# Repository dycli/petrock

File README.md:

# Petrock

A split choc keyboard with a trackpoint in place of an outer thumb key:
**Petrock-41** has one, at the right thumb; **Petrock-40** has one on each half;
**Petrock-42** has none, a key at both outer thumbs.

Based on holykeebs' Corne Choc PCB and plate from
[idank/keyboards](https://github.com/idank/keyboards) (`corne/choc`, commit
f149b9b), licensed CC-BY-SA-4.0. This derivative uses the same licence.

## Changes from the Corne Choc

The board is built from the stock file: its parts move to the new layout, and
every wire is then drawn afresh by rule (see Build). The stock schematic's
connections stay, apart from the thumbs' columns (see Firmware).

- **No lighting.** Every per-key and underglow LED, the LED supply diodes and
  the LED wiring are gone (`tools/no_leds.py`). An RGB version may follow.
- **Exact stagger.** Rows exactly 17 mm apart, each column's top key a whole
  number of 2.37 mm steps below the middle finger's (`tools/stagger.py`;
  stock is off by up to 0.02 mm).
- **Five columns.** The outer pinky column goes. The pinky column moves up to
  one step below the ring column and gains a fourth key (the old outer top
  key); the ring column gains one too (the old outer bottom key). Each joins
  the column wire it lands on, in the thumb row (row 3).
- **Thumb cluster.** Each thumb key turns 15 degrees from its neighbour about a
  hinge where their facing corners sit 0.5 mm apart, starting from the bottom
  inner-index key (`tools/thumbs.py`). The 1.5u inner key becomes two 1u keys;
  the new upper one takes the thumb row's last free column (col 0).
- **Trackpoint.** Sprintek SK8707-01-004 at the outer thumb key: sensor on the
  front, nub centred on where the key was, driver on the back, PS/2 clock and
  data on controller pins 1/2, 3.3 V from the OLED header; sensor A1/A3, controller
  board A2/A4 (`tools/outer_thumb.py`, footprints from `tools/make_footprints.py`).
- **Pins for wireless.** Pins 1/2 are a nice!nano's high-frequency D1/D0, which
  the ZMK PS/2 driver recommends (lower-frequency pins can disturb Bluetooth);
  the TRRS data line moves from pin 2 to pin 11 to free them (`tools/pins.py`).
- **Outline.** Drawn from the keys (`tools/outline.py`): a flat top 1.15 mm
  above the middle column, 7.5-degree slopes to either side, a straight outer
  side, one 7.5-degree bottom edge, and the inner side widened for the upper
  thumb key (`tools/widen.py`). Keycaps sit 1.15 mm from the edge wherever it
  follows them.
- **Controller corner.** Across the strip between the inner index keycaps
  and the inner edge, the controller (a nice!nano's 17.78 mm board) and the
  jack's 6 mm body sit with three even 1.63 mm gaps; each drops until its square
  top corner is 1.15 mm inside the inner slope, like the keycaps. The USB-C and
  the jack's barrel overhang. The reset button sits under the jack
  (`tools/inner_strip.py`).
- The holykeebs and Corne logos and holykeebs' revision stamp are removed; the back
  carries the short hash of the commit the board was built from, between each
  controller's pin rows (`tools/stamp.py`; the build won't stamp uncommitted
  scripts); the board and the switch plates
  carry the Petrock logo with a 7 mm dot in its notch (`tools/logo.py`), and the
  jack, reset button and OLED header have no printed outlines
  (`tools/quiet_silk.py`).
- Five standoffs per half, as stock, placed by geometry (`tools/standoffs.py`):
  four where four keys meet, each at the four keys' centre, forming a 54 x 34 mm
  rectangle (pinky and ring columns, and index and inner index columns, each
  between their top two rows and below their third); and one at the thumbs,
  equally far from its three keycap corners. A key diode may move a fraction to
  make room, if it stays clear. The switch plate has a screw hole over each
  (`tools/plate.py`), as stock.
- Plates regenerated (`tools/plate.py`): the right one (both, on Petrock-40;
  neither, on Petrock-42) has an opening for the trackpoint sensor; a new FR4 bottom plate fits the
  outline.

## Build

`tools/build.sh [single|dual|none]` regenerates a board from the stock file:

1. **Place:** strip the lighting, then move every part to the layout
   (`tools/parts.py drag`).
2. **Route by rule** (`tools/route.py`), as a careful hand would: each column a
   straight line up the front through its switch pins; each row a line along
   the back under its keys, stepping 45 degrees in the gap between columns;
   every diode in the same place beside its key with the same two short links;
   the column wires gathered into an evenly spaced bus in the gap under the
   middle row and fanned into the controller in a staircase; the trackpoint
   wires and power in a bundle up the lane between the middle and index
   columns and along the top edge; every bend 45 degrees, no right angles
   except where a wire joins another. Then ground is poured on both sides and
   stitched together with vias (`tools/stitch.py`).
3. **Check:** the build fails unless DRC finds nothing but the stock
   footprints' library notices and every connection is made.

Then `tools/plates.sh` makes the plates (order the switch plates at 1.2 mm,
which choc switches clip into; the main board and bottom plate at 1.6 mm; all
in HASL, the cheapest finish: the trackpoint driver's pads are hand-soldered
and wide enough that ENIG's flatness isn't needed)
and the 1:1 printout (print it with
scaling off, e.g. `lp -o print-scaling=none`). `tools/fab.sh [single|dual|none]`
writes Gerber and drill zips and JLC's assembly BOM and placement (diodes and
hot-swap sockets) to `fab/`; `tools/demo.sh` renders `demo/`. All need KiCad 10.

Outputs: `pcb/petrock-41*.kicad_pcb` and `pcb/bottom.kicad_pcb`;
`pcb/dual/petrock-40*.kicad_pcb` and `pcb/dual/bottom.kicad_pcb`;
`pcb/none/petrock-42*.kicad_pcb` and `pcb/none/bottom.kicad_pcb`.

## Assembly

The stack, per standoff: a top screw through the switch plate's 2.1 mm hole
into a spacer that passes through the main board's 3.1 mm hole down to the
bottom plate, where a bottom screw holds it. The switch plate and bottom plate
clamp the spacers; the main board hangs from the switches (clipped into the
plate, pins in the hot-swap sockets), 1.0 mm under the plate.

- 10 round M2 x 5 mm female-female spacers, 3.0 mm across (knurled brass ones
  are common; hex ones don't pass the 3.1 mm holes). 5 mm, not holykeebs' 4 mm:
  it leaves 2.4 mm under the main board for the sockets (1.85 mm) and the
  trackpoint drivers (about 2.1 mm).
- Top screws (they sit on the plate, beside the switches): the four where four
  keys meet sit between switch housings (15 mm square on an 18 x 17 mm grid),
  so their heads must be about 3.0 mm across or less: M2 low small-head socket
  screws (e.g. MISUMI's; check the listed head diameter), or M1.6 socket caps
  (3.0 mm heads) with M1.6 spacers at those four. The thumb one and the 10
  underneath: ordinary low M2 x 3 mm screws (e.g. ISO 7380, holykeebs').
- Order: spacers up through the main board, bottom plate on; switch plate on
  and its screws in; then the switches, which draw the main board up as they seat.
- Rubber feet: near the standoffs, and two along the bottom edge (by the outer
  corner and under the trackpoint), which has no standoff.

## Firmware

- Matrix (each half, right with `_r` nets): rows 0-2 are the three full rows,
  columns 1-5 pinky to inner index. Row 3 is the bottom pinky key (col 1), the
  bottom ring key (col 2) and the thumbs, outer to inner: col 3, col 4, col 5.
  Col 0 is unused, except on a half with four thumbs (the 41's left, both of
  the 42's): there the extra outermost one (in the trackpoint's place) is col
  3, the next two col 4 and col 5, and the innermost col 0.
- Wired (QMK, RP2040 Pro Micro): split serial on pin 11 (`SOFT_SERIAL_PIN GP8`,
  PIO driver); PS/2 `PS2_CLOCK_PIN GP0`, `PS2_DATA_PIN GP1` (PIO driver).
- Wireless (ZMK, nice!nano): PS/2 clock D1 (P0.06), data D0 (P0.08), e.g. with
  infused-kim's PS/2 mouse driver; the trackpoint's driver board resets itself,
  so no reset pin. It draws power from the controller's VCC pin, which ZMK's
  external-power control switches off in sleep. The battery solders to the
  nice!nano's B+/B- pads (no switch on the board). The jack isn't used.
- The sensor's pad edge faces the controller (if the axes come out turned,
  rotate them in firmware). No RGB.

## Open items

- **Driver footprint:** Sprintek doesn't draw the detached driver on its own.
  Its outline and sensor-link pads follow the integrated-module drawing. Its
  host pins disagree between the drawing (1.80 mm pitch) and holykeebs'
  product photos (1.72 mm), so their pads fit both: 1.758 mm pitch about the
  row's shared middle, every pin within 0.21 mm of its pad's centre either
  way. Check a real driver against the footprint before ordering boards.
- **Under-board height:** check that the driver (about 2 mm) clears the
  bottom plate.
- **Standoff length** for the plate/PCB/bottom sandwich (M2 3 mm both sides
  expected for the 1.6 mm FR4 bottom).
- **Schematic:** still the Corne Choc's.

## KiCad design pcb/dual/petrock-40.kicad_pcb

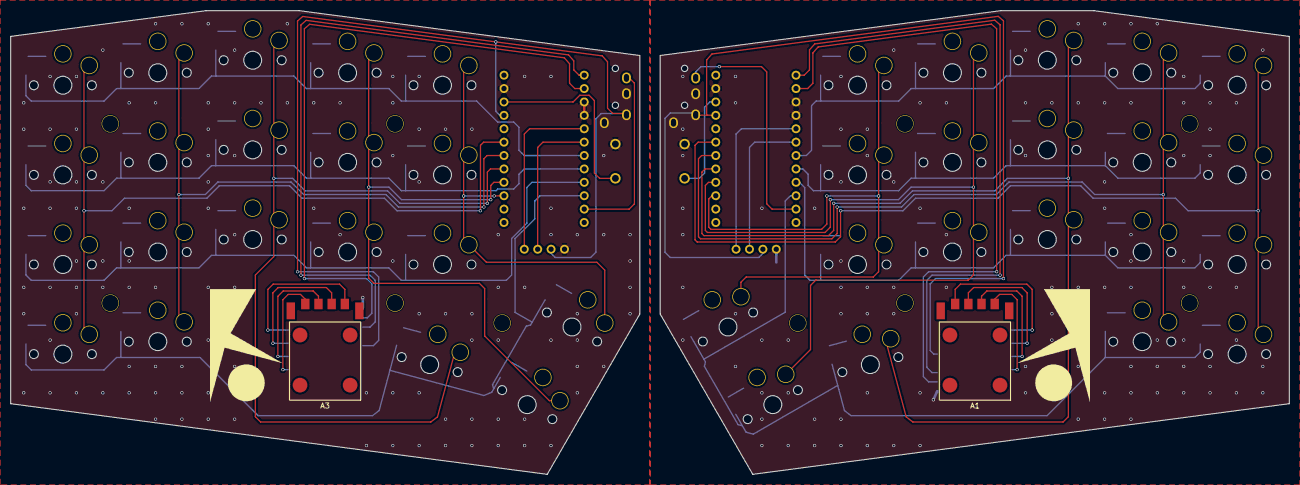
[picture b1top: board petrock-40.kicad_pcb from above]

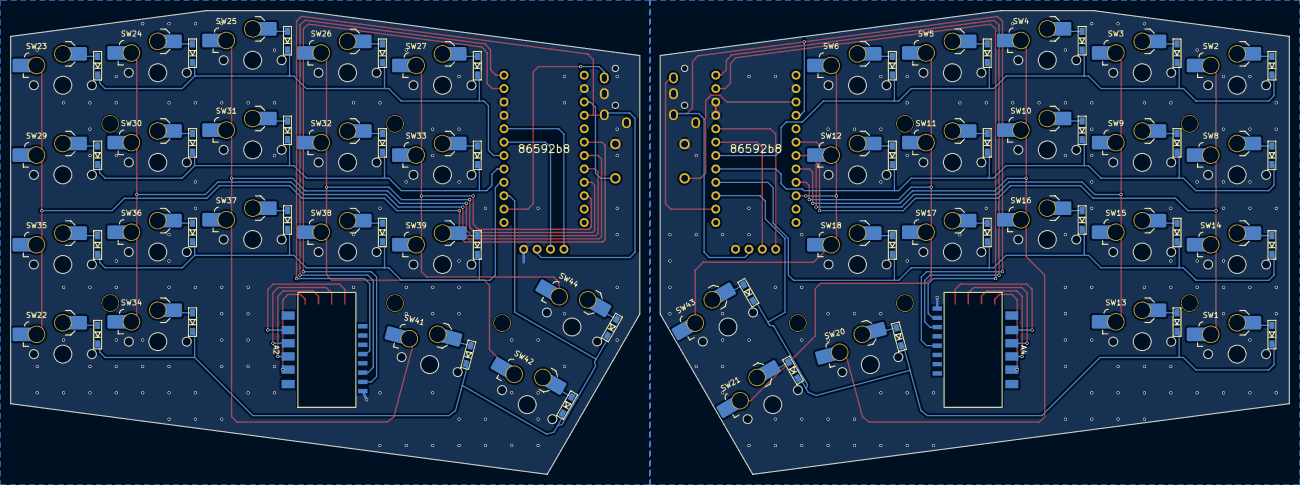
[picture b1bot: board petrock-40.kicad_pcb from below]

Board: 2 copper layers, 242.5 x 87.9 mm, 100 parts (86 on the bottom side), 82 nets.

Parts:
A1, A3: SK8707-01 sensor; SK8707-01_sensor
A2, A4: SK8707-01 driver; SK8707-01_driver
D1, D2, D3, D4, D5, D6, D8, D9, D10, D11, D12, D13, D14, D15, D16, D17, D18, D20, D21, D22, D23, D24, D25, D26, D27, D29, D30, D31, D32, D33, D34, D35, D36, D37, D38, D39, D41, D42, D45, D46: D; D3_SMD_v2
J1, J3: MJ-4PP-9; MJ-4PP-9_1side
J2, J4: OLED; OLED_1side_1mm_holes
RSW1, RSW2: SW_PUSH; ResetSW_1side
SW1, SW2, SW3, SW4, SW5, SW6, SW8, SW9, SW10, SW11, SW12, SW13, SW14, SW15, SW16, SW17, SW18, SW20, SW21, SW22, SW23, SW24, SW25, SW26, SW27, SW29, SW30, SW31, SW32, SW33, SW34, SW35, SW36, SW37, SW38, SW39, SW41, SW42, SW43, SW44: SW_PUSH; SW_choc_v1_HS_CPG135001S30_1u
U1, U2: ProMicro; ProMicro_1mm_holes
h2, h2#2, h2#3, h2#4, h2#5, h2#6, h2#7, h2#8: h2; M2_SPACER

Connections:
GND: A4.1, J1.C, J2.4, RSW1.2, U1.3 (GND), U1.4 (GND), U1.23 (GND)
GNDA: A2.1, J3.C, J4.4, RSW2.2, U2.3 (GND), U2.4 (GND), U2.23 (GND)
unnamed: D1.2 (A), SW1.2
unnamed: D2.2 (A), SW2.2
unnamed: D3.2 (A), SW3.2
unnamed: D4.2 (A), SW4.2
unnamed: D5.2 (A), SW5.2
unnamed: D6.2 (A), SW6.2
unnamed: D8.2 (A), SW8.2
unnamed: D9.2 (A), SW9.2
unnamed: D10.2 (A), SW10.2
unnamed: D11.2 (A), SW11.2
unnamed: D12.2 (A), SW12.2
unnamed: D13.2 (A), SW13.2
unnamed: D14.2 (A), SW14.2
unnamed: D15.2 (A), SW15.2
unnamed: D16.2 (A), SW16.2
unnamed: D17.2 (A), SW17.2
unnamed: D18.2 (A), SW18.2
unnamed: D20.2 (A), SW20.2
unnamed: D21.2 (A), SW21.2
unnamed: D22.2 (A), SW22.2
unnamed: D23.2 (A), SW23.2
unnamed: D24.2 (A), SW24.2
unnamed: D25.2 (A), SW25.2
unnamed: D26.2 (A), SW26.2
unnamed: D27.2 (A), SW27.2
unnamed: D29.2 (A), SW29.2
unnamed: D30.2 (A), SW30.2
unnamed: D31.2 (A), SW31.2
unnamed: D32.2 (A), SW32.2
unnamed: D33.2 (A), SW33.2
unnamed: D34.2 (A), SW34.2
unnamed: D35.2 (A), SW35.2
unnamed: D36.2 (A), SW36.2
unnamed: D37.2 (A), SW37.2
unnamed: D38.2 (A), SW38.2
unnamed: D39.2 (A), SW39.2
unnamed: D41.2 (A), SW41.2
unnamed: D42.2 (A), SW42.2
unnamed: D45.2 (A), SW43.2
unnamed: D46.2 (A), SW44.2
SCL: J2.2, U1.6 (3/D0/SCL)
SCL_r: J4.2, U2.6 (3/D0/SCL)
SDA: J2.1, U1.5 (2/D1/SDA)
SDA_r: J4.1, U2.5 (2/D1/SDA)
TP_CLK: A2.3, U2.1 (TX0/D3)
TP_CLK_L: A4.3, U1.1 (TX0/D3)
TP_DATA: A2.2, U2.2 (RX1/D2)
TP_DATA_L: A4.2, U1.2 (RX1/D2)
TP_S1: A1.S1, A2.S1
TP_S1_L: A3.S1, A4.S1
TP_S2: A1.S2, A2.S2
TP_S2_L: A3.S2, A4.S2
TP_S3: A1.S3, A2.S3
TP_S3_L: A3.S3, A4.S3
TP_S4: A1.S4, A2.S4
TP_S4_L: A3.S4, A4.S4
VCC: A4.5, J1.D, J2.3, U1.21 (VCC)
VDD: A2.5, J3.D, J4.3, U2.21 (VCC)
col1: SW1.1, SW2.1, SW8.1, SW14.1, U1.19 (F5/A2)
col1_r: SW22.1, SW23.1, SW29.1, SW35.1, U2.19 (F5/A2)
col2: SW3.1, SW9.1, SW13.1, SW15.1, U1.18 (F6/A1)
col2_r: SW24.1, SW30.1, SW34.1, SW36.1, U2.18 (F6/A1)
col3: SW4.1, SW10.1, SW16.1, SW20.1, U1.17 (F7/A0)
col3_r: SW25.1, SW31.1, SW37.1, SW41.1, U2.17 (F7/A0)
col4: SW5.1, SW11.1, SW17.1, SW21.1, U1.16 (B1/15)
col4_r: SW26.1, SW32.1, SW38.1, SW42.1, U2.16 (B1/15)
col5: SW6.1, SW12.1, SW18.1, SW43.1, U1.15 (B3/14)
col5_r: SW27.1, SW33.1, SW39.1, SW44.1, U2.15 (B3/14)
data: J1.B, U1.11 (8/B4)
data_r: J3.B, U2.11 (8/B4)
reset: RSW1.1, U1.22 (RST)
reset_r: RSW2.1, U2.22 (RST)
row0: D2.1 (K), D3.1 (K), D4.1 (K), D5.1 (K), D6.1 (K), U1.7 (4/D4)
row0_r: D23.1 (K), D24.1 (K), D25.1 (K), D26.1 (K), D27.1 (K), U2.7 (4/D4)
row1: D8.1 (K), D9.1 (K), D10.1 (K), D11.1 (K), D12.1 (K), U1.8 (5/C6)
row1_r: D29.1 (K), D30.1 (K), D31.1 (K), D32.1 (K), D33.1 (K), U2.8 (5/C6)
row2: D14.1 (K), D15.1 (K), D16.1 (K), D17.1 (K), D18.1 (K), U1.9 (6/D7)
row2_r: D35.1 (K), D36.1 (K), D37.1 (K), D38.1 (K), D39.1 (K), U2.9 (6/D7)
row3: D1.1 (K), D13.1 (K), D20.1 (K), D21.1 (K), D45.1 (K), U1.10 (7/E6)
row3_r: D22.1 (K), D34.1 (K), D41.1 (K), D42.1 (K), D46.1 (K), U2.10 (7/E6)

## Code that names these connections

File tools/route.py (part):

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s43 = L["SW43"](-7, ROW_DY)
track(n3, B, [f21(-7, 0.6), f21(-7.6, 0), f21(-7.6, -12.8), f21(-7, -13.4), s43])
# Then into the controller, down the gap beside the screen header.
px, py = pin_of(row3)
drop = LEFT_PINS + 1.45 + 0.65
lane = INSIDE + 3.0
sq = L["SW43"](-7 - (s43[0] - drop) / math.cos(math.radians(30)), ROW_DY)   # square off the thumb line
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# down to the button.
pr = pin_of("reset")
r1 = pad("RSW1", "1")
far_x = pin_of("row0")[0]
# (out between the data and ground pins, so the two ground pins can be tied together)
track(net("RSW1", "1"), F, [pr, (far_x - 2.11, pr[1]), (far_x - 0.84, pr[1] - 1.27), (far_x + 0.92, pr[1] - 1.27),
                              (145.3, pr[1] - 0.27), (145.3, r1[1] - 1), (146.3, r1[1]), r1])
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    track(net(top, "1"), F, [(x, pad(top, "1", tht=True)[1]), (x, pad(bot, "1", tht=True)[1])])
# Rows 0..2 under the keys, inwards, then down a lane beside the controller's
# near pins and straight in.
NEAR = pin_of("row0_r")[0]
for i in range(3):
    n = net(rdiode[rmain[(0, i)]], "1")
    pts = []
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# up to the front, under the controller and up its outer side into the far pins.
ncol = len(rcols)
rcy1 = [rk[rmain[(c, 1)]][1] for c in range(ncol)]
FAR = pin_of("col1_r")[0]
for c in range(ncol):
    k = (ncol - 1) - c                     # wire level: the inner column's on top, the pinky's at the bottom
    n = net(rmain[(c, 0)], "1")
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s44 = RL["SW44"](-7, ROW_DY)
track(n3r, B, [f42(-7, 0.6), f42(-7.6, 0), f42(-7.6, -12.8), f42(-7, -13.4), s44])
p44, w44 = along(RL["SW44"], (-7, ROW_DY), (0, ROW_DY))
px, py = pin_of("row3_r")
up3 = px - 2.05
track(n3r, B, [s44, meet(p44, w44, (up3, 0), (0, 1)), (up3, py + 1), (up3 + 1, py), (px, py)])
# Thumb columns on the front.
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j3, jd = pad("J4", "3"), pad("J3", "D")
track(net("J4", "3"), B, [j3, (j3[0], 98.6), (159.7, 98.6), (158.7, 97.6), (158.7, 72.2), (159.7, 71.2), (jd[0], 71.2)])
# Reset: on the back, down beside the controller's far pins to the button.
pr, r1 = pin_of("reset_r"), pad("RSW2", "1")
track(net("RSW2", "1"), B, [pr, (166.2, pr[1]), (166.2, r1[1] - 1), (165.2, r1[1]), r1])
# Jack data: across inside the controller on the front, over its top on the back.
pdx, jb = pin_of("data_r"), pad("J3", "B")
track(net("J3", "B"), F, [pdx, (178.0, pdx[1]), (178.0, 63.4), (177.0, 62.4), (169.0, 62.4)])
via(net("J3", "B"), (169.0, 62.4))
track(net("J3", "B"), B, [(169.0, 62.4), (jb[0], 62.4), jb])
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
